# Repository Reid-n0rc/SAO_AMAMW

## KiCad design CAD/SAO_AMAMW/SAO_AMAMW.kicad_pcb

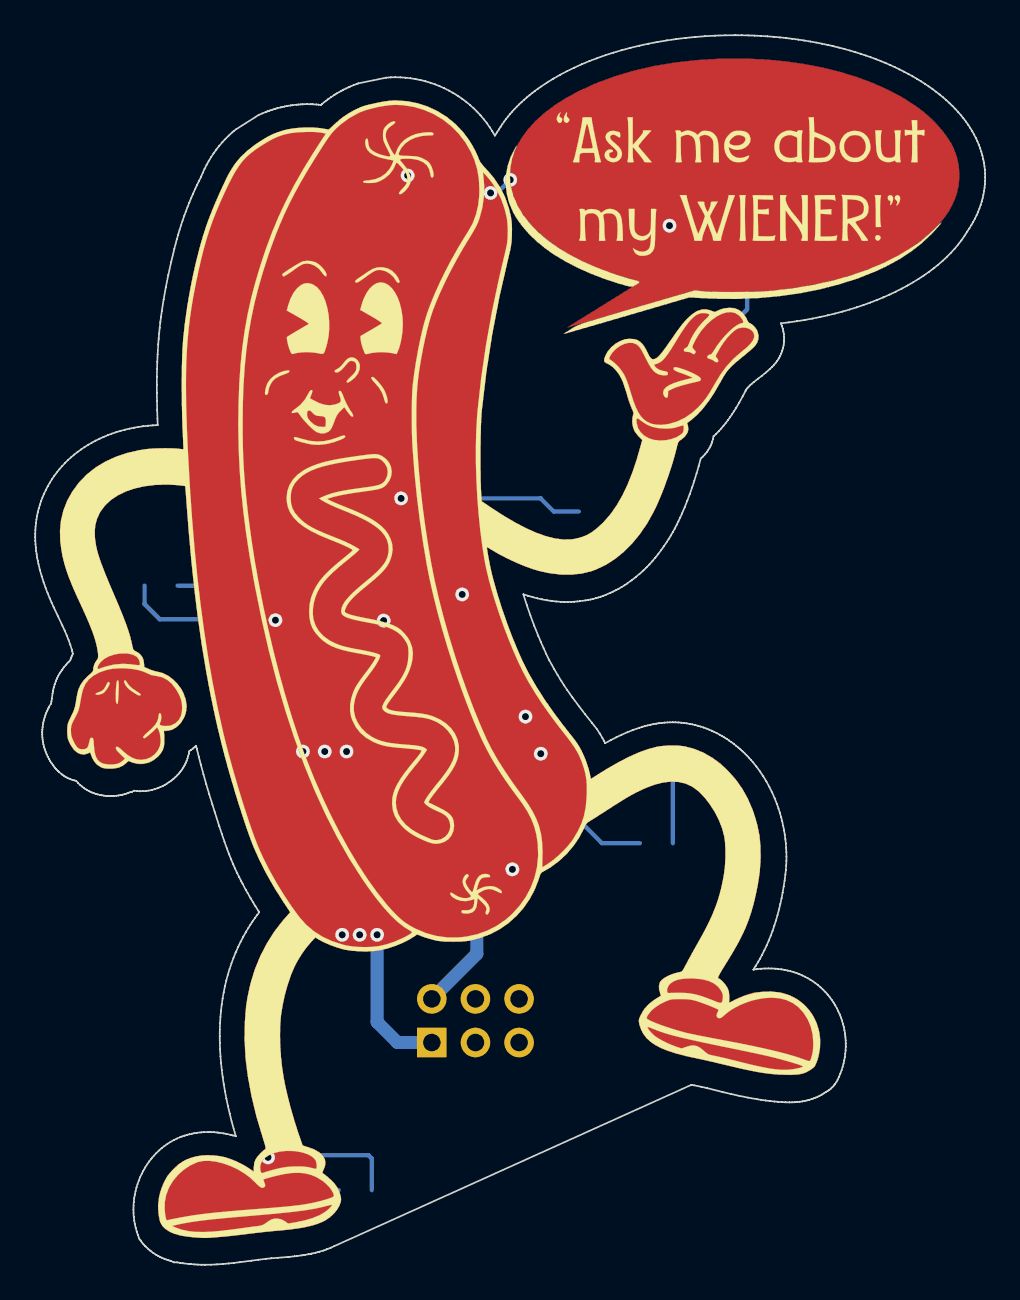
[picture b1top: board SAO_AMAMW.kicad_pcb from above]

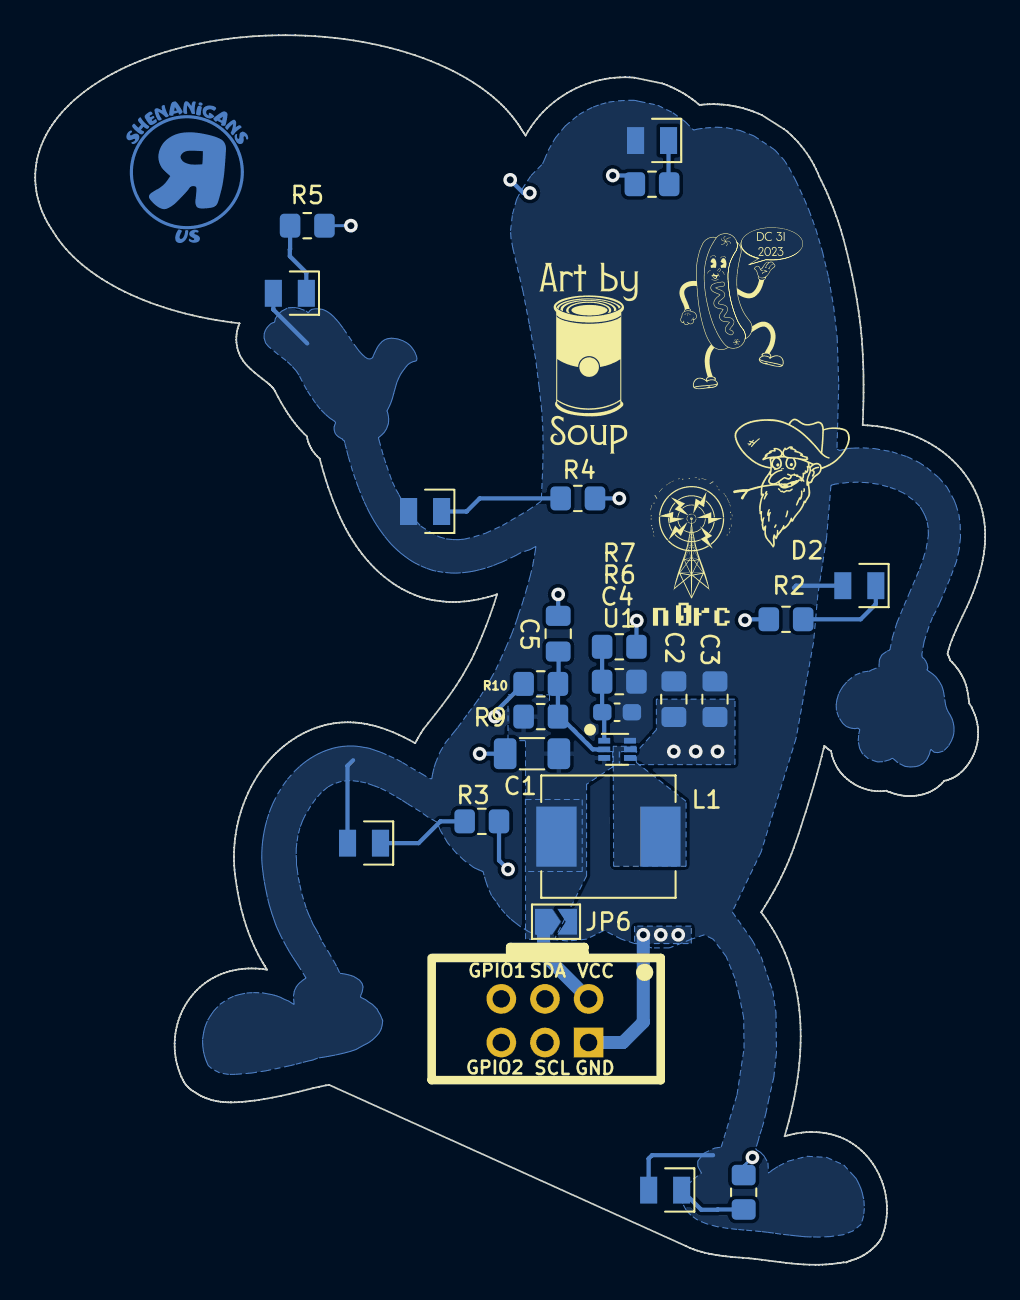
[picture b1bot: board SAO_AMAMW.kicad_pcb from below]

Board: 2 copper layers, 55.3 x 71.6 mm, 26 parts (24 on the bottom side), 12 nets.

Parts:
C1: 10uF; C_1206_3216Metric_Pad1.33x1.80mm_HandSolder
C2, C3, C5: 10uF; C_0805_2012Metric_Pad1.18x1.45mm_HandSolder
C4: 1pF; C_0603_1608Metric_Pad1.08x0.95mm_HandSolder
D1, D2, D3, D4, D5, D6: LED; LED_0807
J1: Badgelife_sao_connector_v169bis; Badgelife-SAOv169-SAO_Side_B.SLK
JP6: SolderJumper_2_Open; SolderJumper-2_P1.3mm_Open_TrianglePad1.0x1.5mm
L1: 1uH; L_Chilisin_BMRx00060630
R1, R2, R3, R4, R5, R8: 56; R_0805_2012Metric_Pad1.20x1.40mm_HandSolder
R6: 499K; R_0805_2012Metric_Pad1.20x1.40mm_HandSolder
R7, R10: 100K; R_0805_2012Metric_Pad1.20x1.40mm_HandSolder
R9: 66.5K; R_0805_2012Metric_Pad1.20x1.40mm_HandSolder
U1: TPS61023; SOT-563
X1: AMAMW

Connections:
+3.3V: C1.1, J1.1 (VCC), JP6.1 (A), L1.1, R9.1, U1.3 (IN)
+3V6: C2.1, C3.1, C4.1, D1.2 (A), D2.2 (A), D3.2 (A), D4.2 (A), D5.2 (A), D6.2 (A), JP6.2 (B), R6.1, U1.6 (OUT)
/EN: C5.1, R9.2, R10.1, U1.2 (EN)
/SW_FB: C4.2, R6.2, R7.1, U1.1 (FB)
/SW_SW: L1.2, U1.5 (SW)
GND: C1.2, C2.2, C3.2, C5.2, J1.2 (GND), R1.2, R2.2, R3.2, R4.2, R5.2, R7.2, R8.2, R10.2, U1.4 (GND), X1.1, X1.2
unnamed: D1.1 (K), R1.1
unnamed: D2.1 (K), R2.1
unnamed: D3.1 (K), R3.1
unnamed: D4.1 (K), R4.1
unnamed: D5.1 (K), R5.1
unnamed: D6.1 (K), R8.1

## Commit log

2024-06-13 Import
2024-06-13 Added broken CI/CD and submodule
2024-06-13 Updates with new SAO footprint
    Updated SAO Footprint. Moved LEDs so they all have the same orientation.
2024-06-13 Update LICENSE
2024-06-17 Stamps in .svg format
    File > Import > Graphics
    Look for the SVG location and change the graphic layer
2024-06-17 Soup Stamp
2024-06-17 n0rc Stamp
2024-06-17 JiggleBilly Stamp with Googles
2024-06-17 JiggleBilly Stamp without Googles
2024-06-18 n0rc, Use these files!
2024-06-18 Fixed font and other issues.
2024-07-03 Updates for fab
2024-07-03 ignore lock files
2024-07-03 added stamps
2024-07-04 Production updates
2024-07-10 Production files
2024-07-17 Updated BOM
